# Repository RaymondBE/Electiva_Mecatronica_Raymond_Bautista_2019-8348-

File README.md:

# Electiva_Mecatronica_Raymond_Bautista_2019-8348-
Repositorio correspondiente a la asignatura de Diseño Mecatrónico. Raymond Bautista Espinosa (2019-8348).

Saludos:
Este repositorio contiene mis entregas realizadas en la asignatura de Diseño Mecatrónico. Período: 2022-C2, Universidad: ITLA.

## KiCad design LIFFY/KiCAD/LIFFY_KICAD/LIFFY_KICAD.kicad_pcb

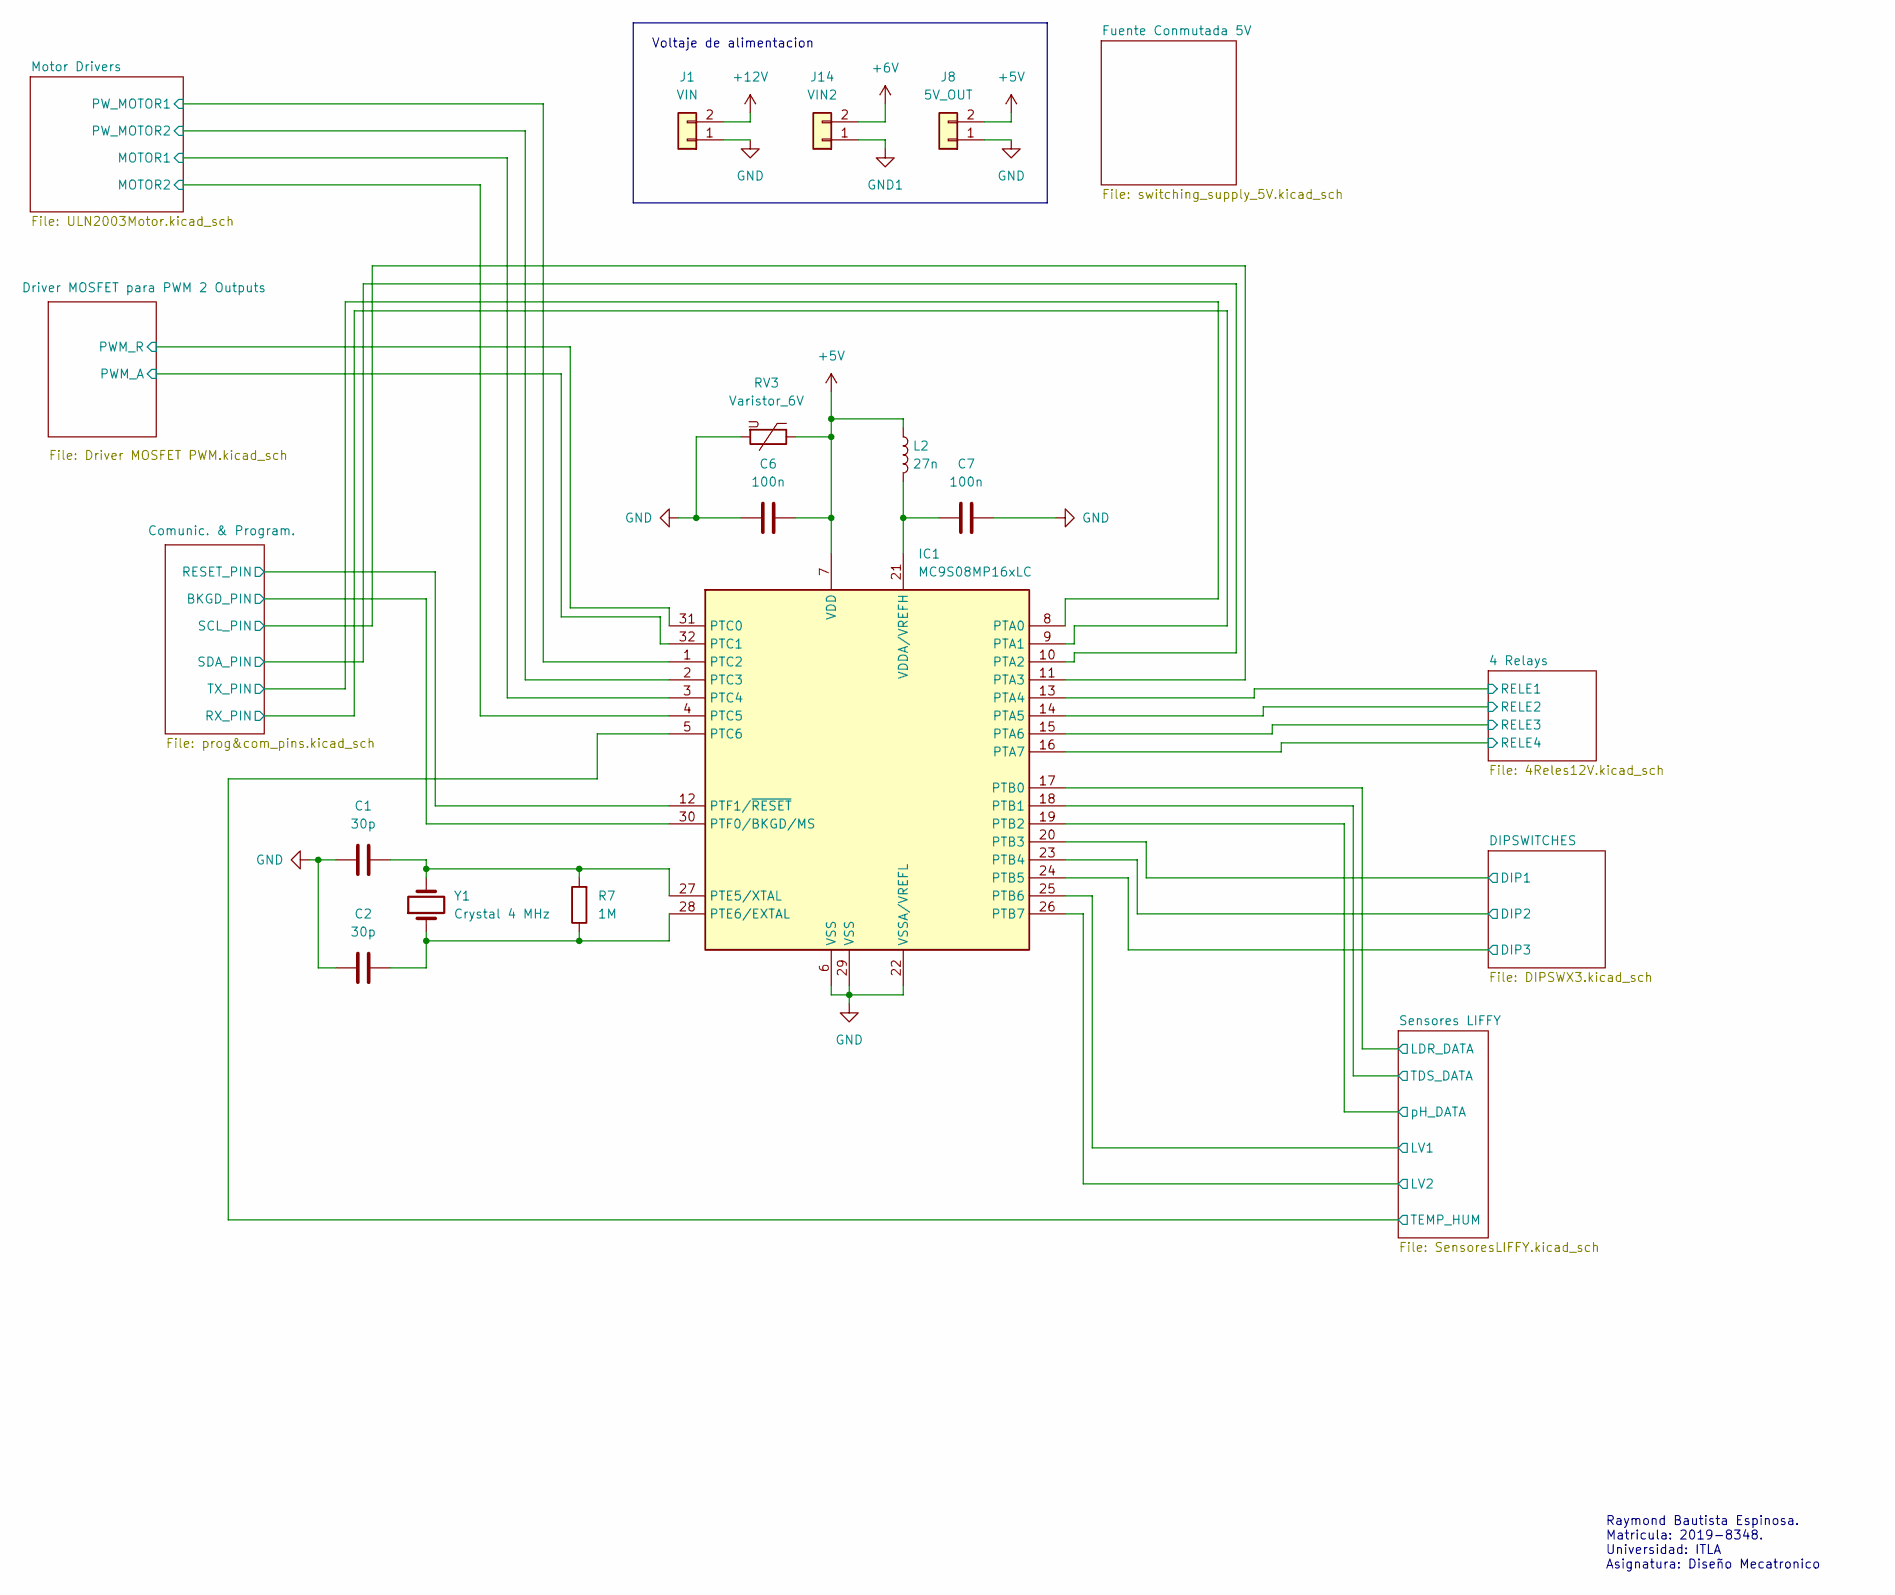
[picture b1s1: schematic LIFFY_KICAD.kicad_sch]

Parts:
C1, C2: 30p; C_0201_0603Metric
C6, C7: 100n; C_0201_0603Metric
IC1: MC9S08MP16xLC; LQFP-32_7x7mm_P0.8mm
J1: VIN; TerminalBlock_bornier-2_P5.08mm
J8: 5V_OUT; TerminalBlock_bornier-2_P5.08mm
J14: VIN2; TerminalBlock_bornier-2_P5.08mm
L2: 27n; L_0805_2012Metric
R7: 1M; R_0201_0603Metric
RV3: Varistor_6V; C_0805_2012Metric
Y1: Crystal 4 MHz; Crystal_HC49-4H_Vertical

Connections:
+5V: C6.2, IC1.7 (VDD), J8.2, L2.1, RV3.1; also elsewhere on the board
+6V: J14.2; also elsewhere on the board
+12V: J1.2; also elsewhere on the board
/4 Relays/RELE1: IC1.13 (PTA4); also elsewhere on the board
/4 Relays/RELE2: IC1.14 (PTA5); also elsewhere on the board
/4 Relays/RELE3: IC1.15 (PTA6); also elsewhere on the board
/4 Relays/RELE4: IC1.16 (PTA7); also elsewhere on the board
/Comunic. & Program./BKGD_PIN: IC1.30 (PTF0/BKGD/MS); also elsewhere on the board
/Comunic. & Program./RESET_PIN: IC1.12 (PTF1/~RESET); also elsewhere on the board
/Comunic. & Program./RX_PIN: IC1.9 (PTA1); also elsewhere on the board
/Comunic. & Program./SCL_PIN: IC1.11 (PTA3); also elsewhere on the board
/Comunic. & Program./SDA_PIN: IC1.10 (PTA2); also elsewhere on the board
/Comunic. & Program./TX_PIN: IC1.8 (PTA0); also elsewhere on the board
/DIPSWITCHES/DIP1: IC1.20 (PTB3); also elsewhere on the board
/DIPSWITCHES/DIP2: IC1.23 (PTB4); also elsewhere on the board
/DIPSWITCHES/DIP3: IC1.24 (PTB5); also elsewhere on the board
/Driver MOSFET para PWM 2 Outputs/PWM_A: IC1.32 (PTC1); also elsewhere on the board
/Driver MOSFET para PWM 2 Outputs/PWM_R: IC1.31 (PTC0); also elsewhere on the board
/Motor Drivers/MOTOR1: IC1.3 (PTC4); also elsewhere on the board
/Motor Drivers/MOTOR2: IC1.4 (PTC5); also elsewhere on the board
/Motor Drivers/PW_MOTOR1: IC1.1 (PTC2); also elsewhere on the board
/Motor Drivers/PW_MOTOR2: IC1.2 (PTC3); also elsewhere on the board
/Sensores LIFFY/LDR_DATA: IC1.17 (PTB0); also elsewhere on the board
/Sensores LIFFY/LV1: IC1.25 (PTB6); also elsewhere on the board
/Sensores LIFFY/LV2: IC1.26 (PTB7); also elsewhere on the board
/Sensores LIFFY/TDS_DATA: IC1.18 (PTB1); also elsewhere on the board
/Sensores LIFFY/TEMP_HUM: IC1.5 (PTC6); also elsewhere on the board
/Sensores LIFFY/pH_DATA: IC1.19 (PTB2); also elsewhere on the board
GND: C1.1, C2.1, C6.1, C7.1, IC1.6 (VSS), IC1.22 (VSSA/VREFL), IC1.29 (VSS), J1.1, J8.1, RV3.2; also elsewhere on the board
GND1: J14.1; also elsewhere on the board
unnamed: C1.2, IC1.27 (PTE5/XTAL), R7.2, Y1.2
unnamed: C2.2, IC1.28 (PTE6/EXTAL), R7.1, Y1.1
unnamed: C7.2, IC1.21 (VDDA/VREFH), L2.2

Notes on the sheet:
Raymond Bautista Espinosa. Matricula: 2019-8348. Universidad: ITLA Asignatura: Diseño Mecatronico
Voltaje de alimentacion

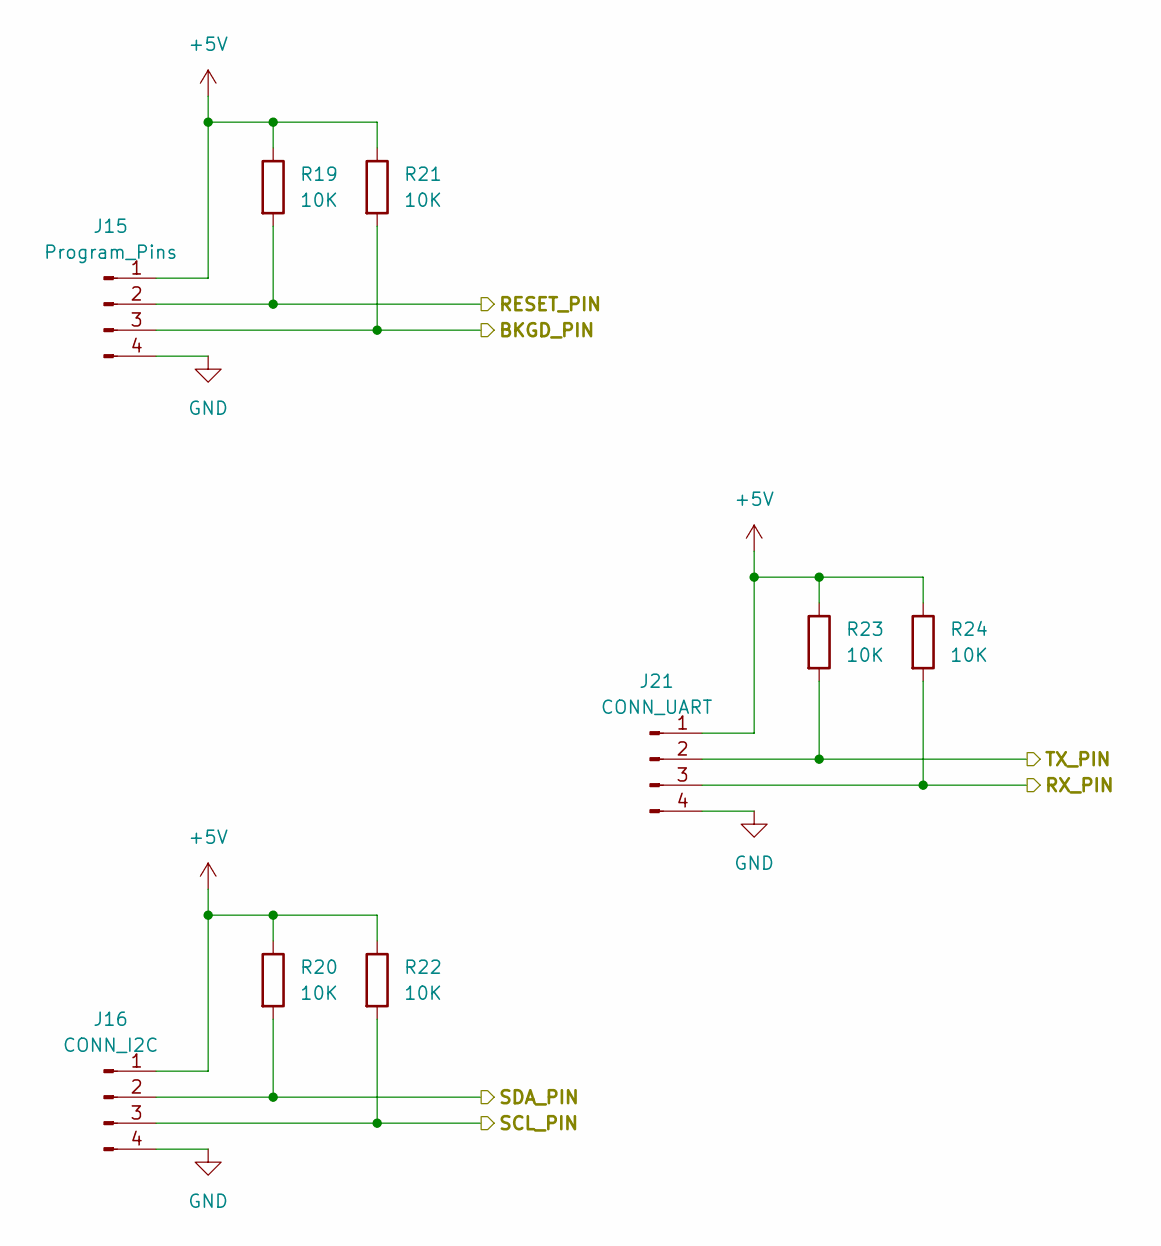
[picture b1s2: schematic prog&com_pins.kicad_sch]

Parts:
J15: Program_Pins; PinHeader_1x04_P2.54mm_Vertical
J16: CONN_I2C; PinHeader_1x04_P2.54mm_Vertical
J21: CONN_UART; PinHeader_1x04_P2.54mm_Vertical
R19, R20, R21, R22, R23, R24: 10K; R_0201_0603Metric

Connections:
+5V: J15.1, J16.1, J21.1, R19.1, R20.1, R21.1, R22.1, R23.1, R24.1; also elsewhere on the board
/Comunic. & Program./BKGD_PIN: J15.3, R21.2; also elsewhere on the board
/Comunic. & Program./RESET_PIN: J15.2, R19.2; also elsewhere on the board
/Comunic. & Program./RX_PIN: J21.3, R24.2; also elsewhere on the board
/Comunic. & Program./SCL_PIN: J16.3, R22.2; also elsewhere on the board
/Comunic. & Program./SDA_PIN: J16.2, R20.2; also elsewhere on the board
/Comunic. & Program./TX_PIN: J21.2, R23.2; also elsewhere on the board
GND: J15.4, J16.4, J21.4; also elsewhere on the board

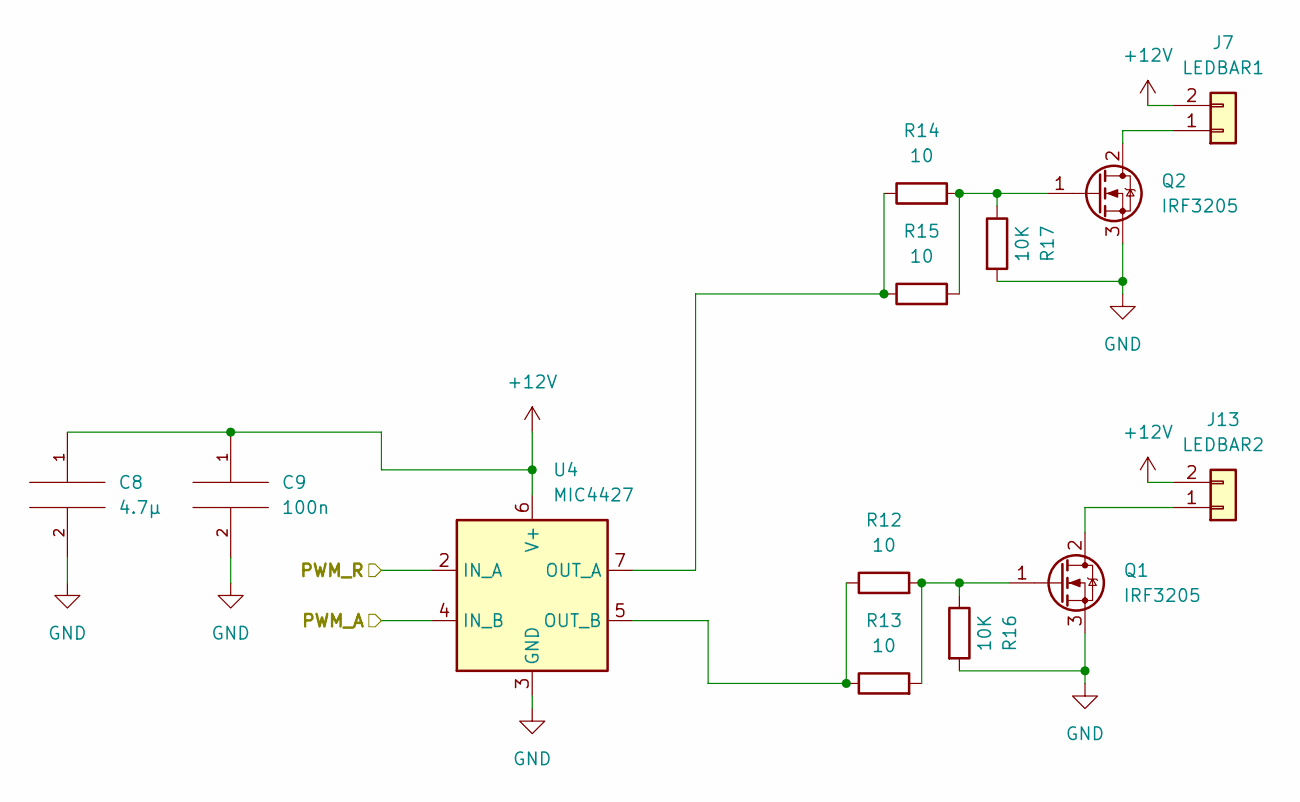
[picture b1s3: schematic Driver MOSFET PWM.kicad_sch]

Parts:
C8: 4.7µ; C_0805_2012Metric
C9: 100n; C_0201_0603Metric
J7: LEDBAR1; TerminalBlock_bornier-2_P5.08mm
J13: LEDBAR2; TerminalBlock_bornier-2_P5.08mm
Q1, Q2: IRF3205; TO-220-3_Vertical
R12, R13, R14, R15: 10; R_0201_0603Metric
R16, R17: 10K; R_0201_0603Metric
U4: MIC4427; SOIC-8_3.9x4.9mm_P1.27mm

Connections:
+12V: C8.1, C9.1, J7.2, J13.2, U4.6 (V+); also elsewhere on the board
/Driver MOSFET para PWM 2 Outputs/PWM_A: U4.4 (IN_B); also elsewhere on the board
/Driver MOSFET para PWM 2 Outputs/PWM_R: U4.2 (IN_A); also elsewhere on the board
GND: C8.2, C9.2, Q1.3 (S), Q2.3 (S), R16.2, R17.2, U4.3 (GND); also elsewhere on the board
unnamed: J7.1, Q2.2 (D)
unnamed: J13.1, Q1.2 (D)
unnamed: Q1.1 (G), R12.2, R13.2, R16.1
unnamed: Q2.1 (G), R14.2, R15.2, R17.1
unnamed: R12.1, R13.1, U4.5 (OUT_B)
unnamed: R14.1, R15.1, U4.7 (OUT_A)

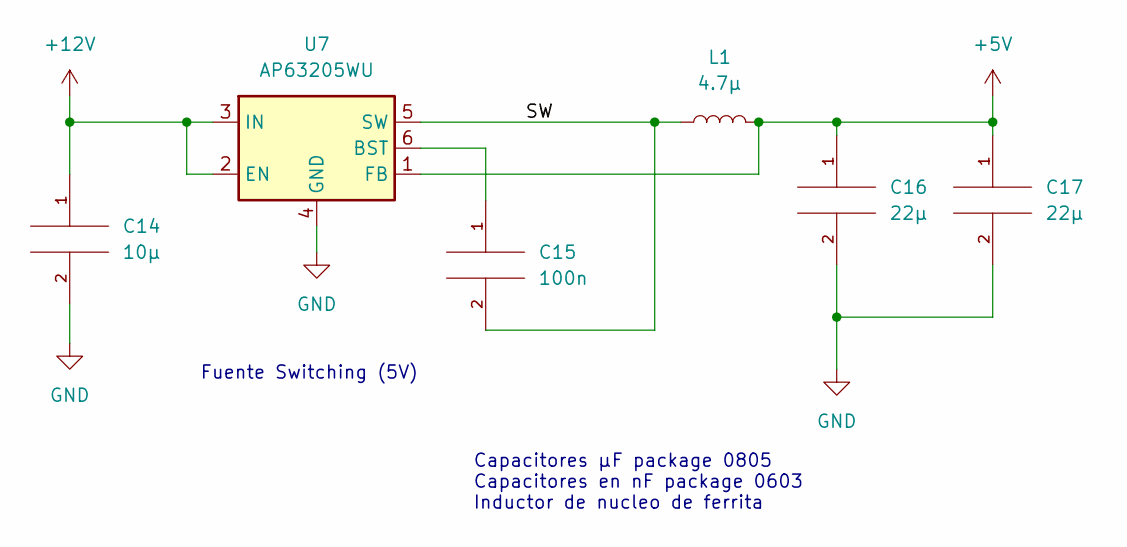
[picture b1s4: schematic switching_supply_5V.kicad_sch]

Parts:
C14: 10µ; C_0805_2012Metric
C15: 100n; C_0201_0603Metric
C16, C17: 22µ; C_0805_2012Metric
L1: 4.7µ; L_Bourns_SRN6045TA
U7: AP63205WU; TSOT-23-6

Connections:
+5V: C16.1, C17.1, L1.2, U7.1 (FB); also elsewhere on the board
+12V: C14.1, U7.2 (EN), U7.3 (IN); also elsewhere on the board
/Fuente Conmutada 5V/SW: C15.2, L1.1, U7.5 (SW)
GND: C14.2, C16.2, C17.2, U7.4 (GND); also elsewhere on the board
unnamed: C15.1, U7.6 (BST)

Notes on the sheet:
Fuente Switching (5V)
Capacitores µF package 0805 Capacitores en nF package 0603 Inductor de nucleo de ferrita

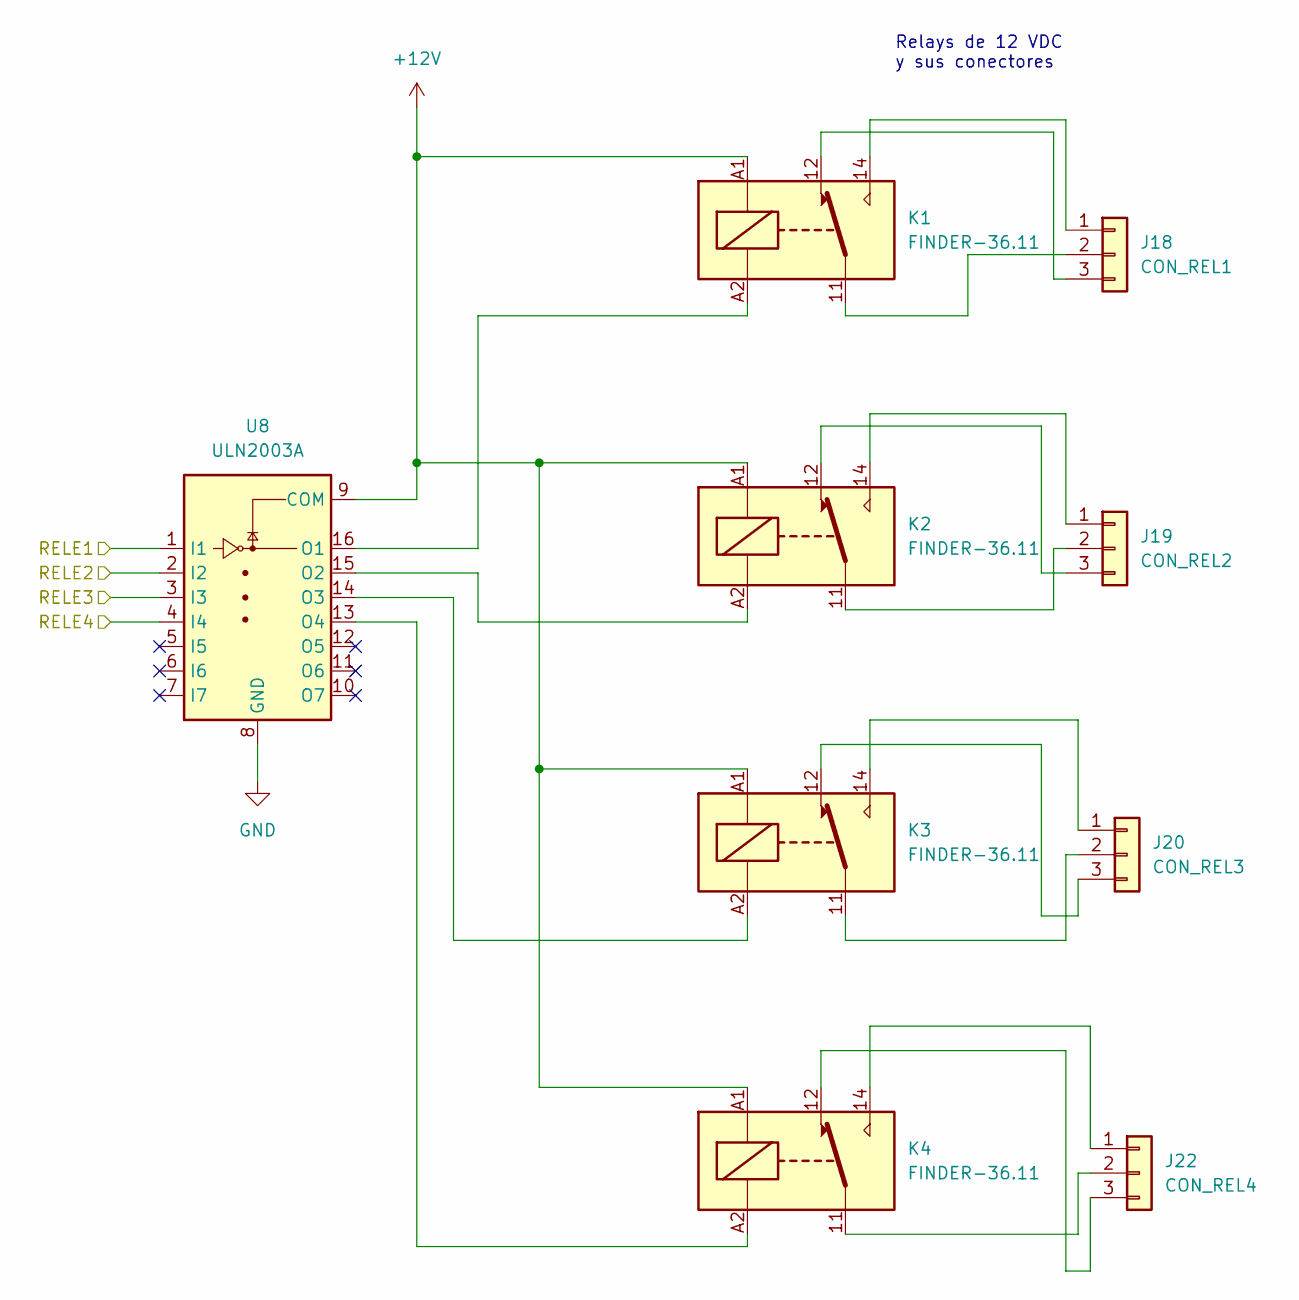
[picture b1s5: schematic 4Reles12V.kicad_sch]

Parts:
J18: CON_REL1; TerminalBlock_bornier-3_P5.08mm
J19: CON_REL2; TerminalBlock_bornier-3_P5.08mm
J20: CON_REL3; TerminalBlock_bornier-3_P5.08mm
J22: CON_REL4; TerminalBlock_bornier-3_P5.08mm
K1, K2, K3, K4: FINDER-36.11; Relay_SPDT_Finder_36.11
U8: ULN2003A; SOIC-16_3.9x9.9mm_P1.27mm

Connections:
+12V: K1.A1, K2.A1, K3.A1, K4.A1, U8.9 (COM); also elsewhere on the board
/4 Relays/RELE1: U8.1 (I1); also elsewhere on the board
/4 Relays/RELE2: U8.2 (I2); also elsewhere on the board
/4 Relays/RELE3: U8.3 (I3); also elsewhere on the board
/4 Relays/RELE4: U8.4 (I4); also elsewhere on the board
GND: U8.8 (GND); also elsewhere on the board
unnamed: J18.1, K1.14
unnamed: J18.2, K1.11
unnamed: J18.3, K1.12
unnamed: J19.1, K2.14
unnamed: J19.2, K2.11
unnamed: J19.3, K2.12
unnamed: J20.1, K3.14
unnamed: J20.2, K3.11
unnamed: J20.3, K3.12
unnamed: J22.1, K4.14
unnamed: J22.2, K4.11
unnamed: J22.3, K4.12
unnamed: K1.A2, U8.16 (O1)
unnamed: K2.A2, U8.15 (O2)
unnamed: K3.A2, U8.14 (O3)
unnamed: K4.A2, U8.13 (O4)

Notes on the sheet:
Relays de 12 VDC y sus conectores

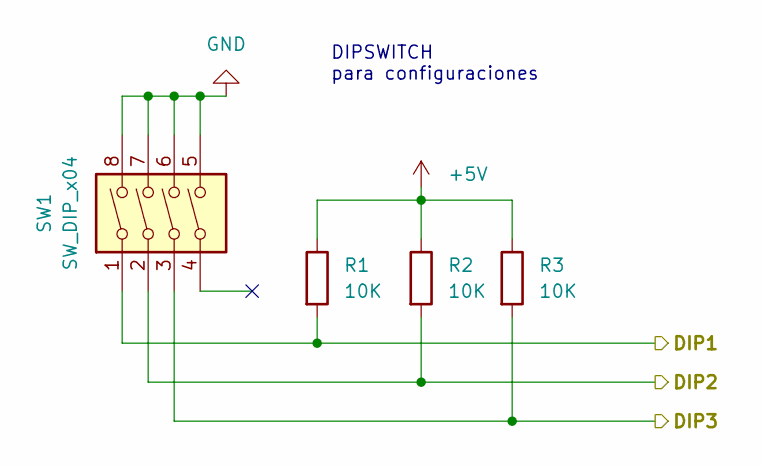
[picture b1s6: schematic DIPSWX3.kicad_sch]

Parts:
R1, R2, R3: 10K; R_0201_0603Metric
SW1: SW_DIP_x04; SW_DIP_SPSTx04_Slide_9.78x12.34mm_W8.61mm_P2.54mm

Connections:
+5V: R1.1, R2.1, R3.1; also elsewhere on the board
/DIPSWITCHES/DIP1: R1.2, SW1.1; also elsewhere on the board
/DIPSWITCHES/DIP2: R2.2, SW1.2; also elsewhere on the board
/DIPSWITCHES/DIP3: R3.2, SW1.3; also elsewhere on the board
GND: SW1.5, SW1.6, SW1.7, SW1.8; also elsewhere on the board

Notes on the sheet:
DIPSWITCH para configuraciones

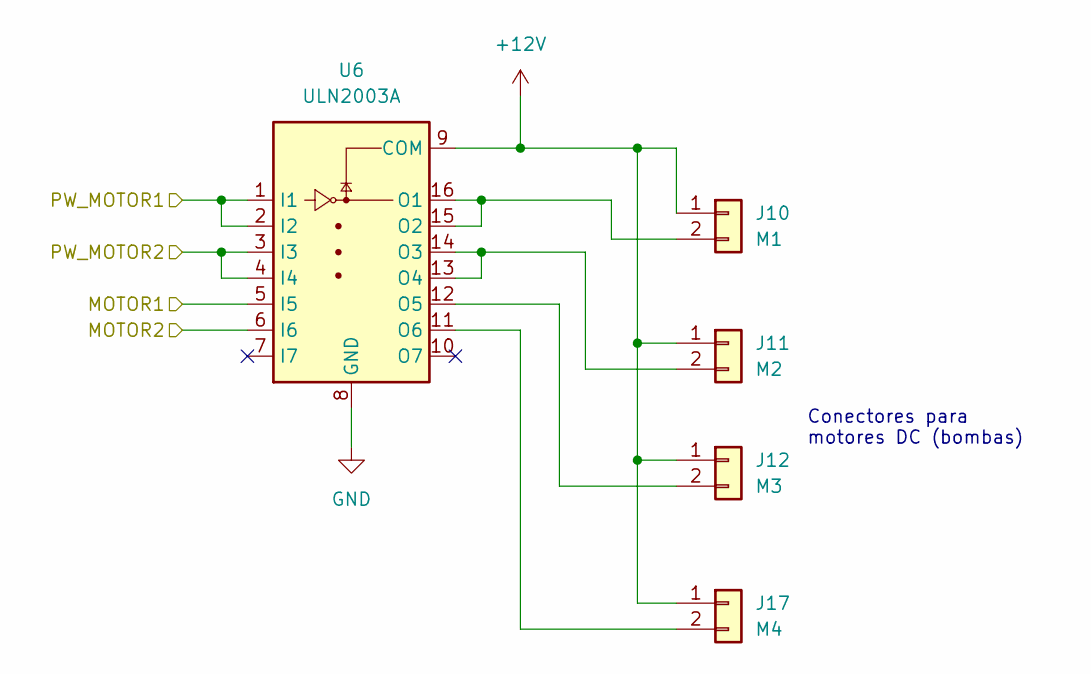
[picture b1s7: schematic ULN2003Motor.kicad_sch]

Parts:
J10: M1; TerminalBlock_bornier-2_P5.08mm
J11: M2; TerminalBlock_bornier-2_P5.08mm
J12: M3; TerminalBlock_bornier-2_P5.08mm
J17: M4; TerminalBlock_bornier-2_P5.08mm
U6: ULN2003A; SOIC-16_3.9x9.9mm_P1.27mm

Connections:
+12V: J10.1, J11.1, J12.1, J17.1, U6.9 (COM); also elsewhere on the board
/Motor Drivers/MOTOR1: U6.5 (I5); also elsewhere on the board
/Motor Drivers/MOTOR2: U6.6 (I6); also elsewhere on the board
/Motor Drivers/PW_MOTOR1: U6.1 (I1), U6.2 (I2); also elsewhere on the board
/Motor Drivers/PW_MOTOR2: U6.3 (I3), U6.4 (I4); also elsewhere on the board
GND: U6.8 (GND); also elsewhere on the board
unnamed: J10.2, U6.15 (O2), U6.16 (O1)
unnamed: J11.2, U6.13 (O4), U6.14 (O3)
unnamed: J12.2, U6.12 (O5)
unnamed: J17.2, U6.11 (O6)

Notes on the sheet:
Conectores para motores DC (bombas)

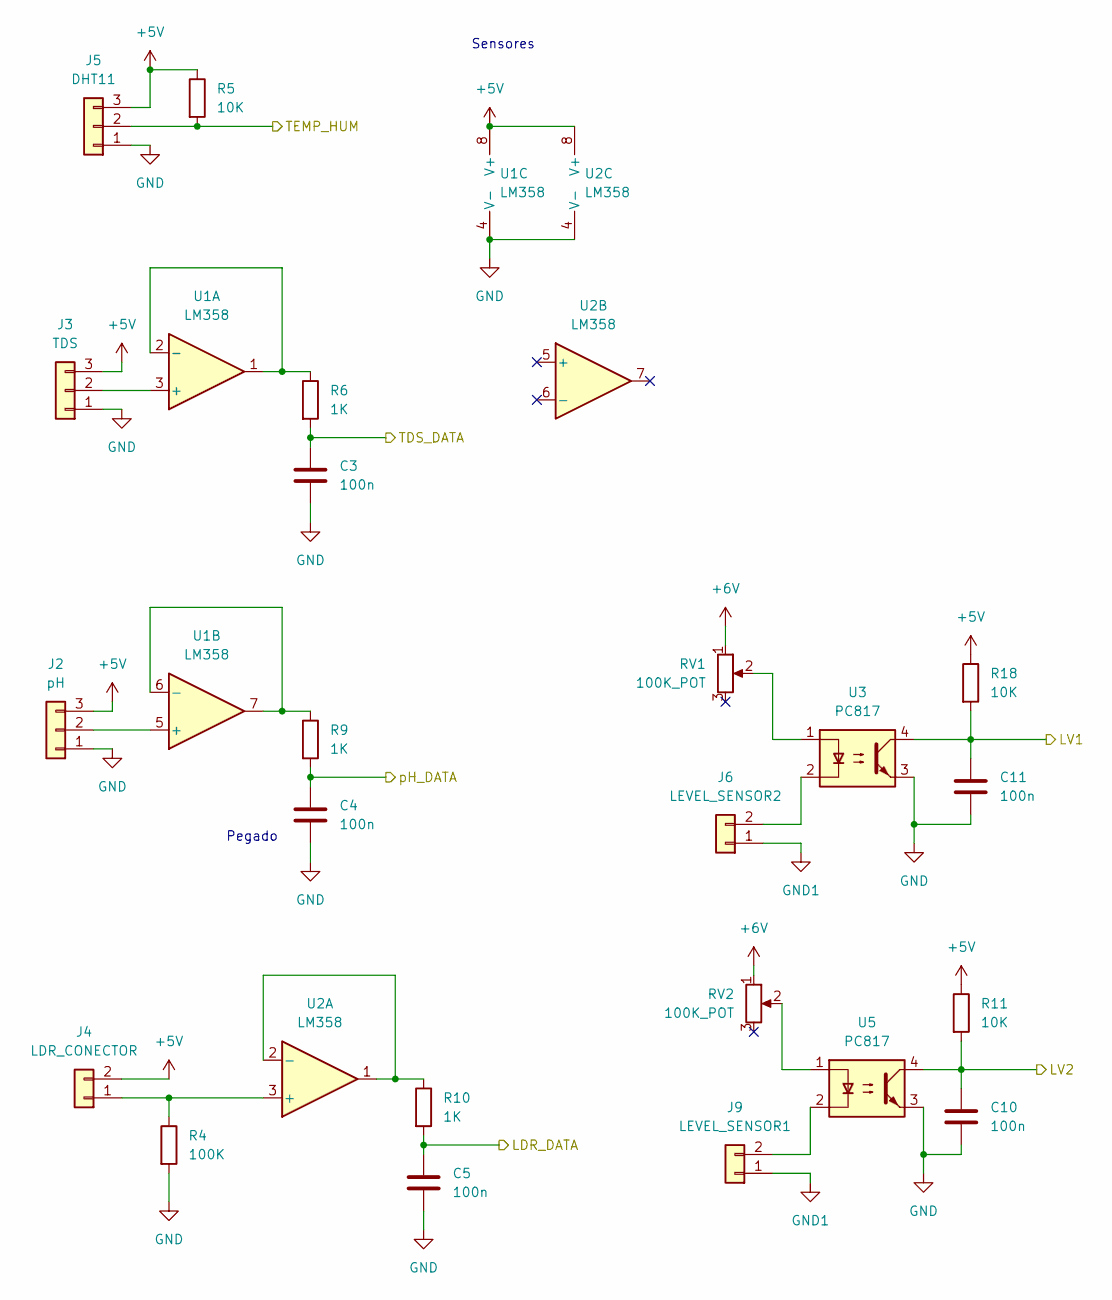
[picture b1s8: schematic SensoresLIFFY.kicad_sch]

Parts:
C3, C4, C5, C10, C11: 100n; C_0201_0603Metric
J2: pH; TerminalBlock_bornier-3_P5.08mm
J3: TDS; TerminalBlock_bornier-3_P5.08mm
J4: LDR_CONECTOR; TerminalBlock_bornier-2_P5.08mm
J5: DHT11; TerminalBlock_bornier-3_P5.08mm
J6: LEVEL_SENSOR2; TerminalBlock_bornier-2_P5.08mm
J9: LEVEL_SENSOR1; TerminalBlock_bornier-2_P5.08mm
R4: 100K; R_0201_0603Metric
R5, R11, R18: 10K; R_0201_0603Metric
R6, R9, R10: 1K; R_0201_0603Metric
RV1, RV2: 100K_POT; Potentiometer_Bourns_3296Y_Vertical
U1, U2: LM358; SOIC-8_3.9x4.9mm_P1.27mm
U3, U5: PC817; SMDIP-4_W7.62mm

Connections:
+5V: J2.3, J3.3, J4.2, J5.3, R5.1, R11.1, R18.1, U1.8 (V+), U2.8 (V+); also elsewhere on the board
+6V: RV1.1, RV2.1; also elsewhere on the board
/Sensores LIFFY/LDR_DATA: C5.1, R10.2; also elsewhere on the board
/Sensores LIFFY/LV1: C11.1, R18.2, U3.4; also elsewhere on the board
/Sensores LIFFY/LV2: C10.1, R11.2, U5.4; also elsewhere on the board
/Sensores LIFFY/TDS_DATA: C3.1, R6.2; also elsewhere on the board
/Sensores LIFFY/TEMP_HUM: J5.2, R5.2; also elsewhere on the board
/Sensores LIFFY/pH_DATA: C4.1, R9.2; also elsewhere on the board
GND: C3.2, C4.2, C5.2, C10.2, C11.2, J2.1, J3.1, J5.1, R4.2, U1.4 (V-), U2.4 (V-), U3.3, U5.3; also elsewhere on the board
GND1: J6.1, J9.1; also elsewhere on the board
unnamed: J2.2, U1.5 (+)
unnamed: J3.2, U1.3 (+)
unnamed: J4.1, R4.1, U2.3 (+)
unnamed: J6.2, U3.2
unnamed: J9.2, U5.2
unnamed: R6.1, U1.1, U1.2 (-)
unnamed: R9.1, U1.6 (-), U1.7
unnamed: R10.1, U2.1, U2.2 (-)
unnamed: RV1.2, U3.1
unnamed: RV2.2, U5.1

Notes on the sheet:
Sensores
Pegado

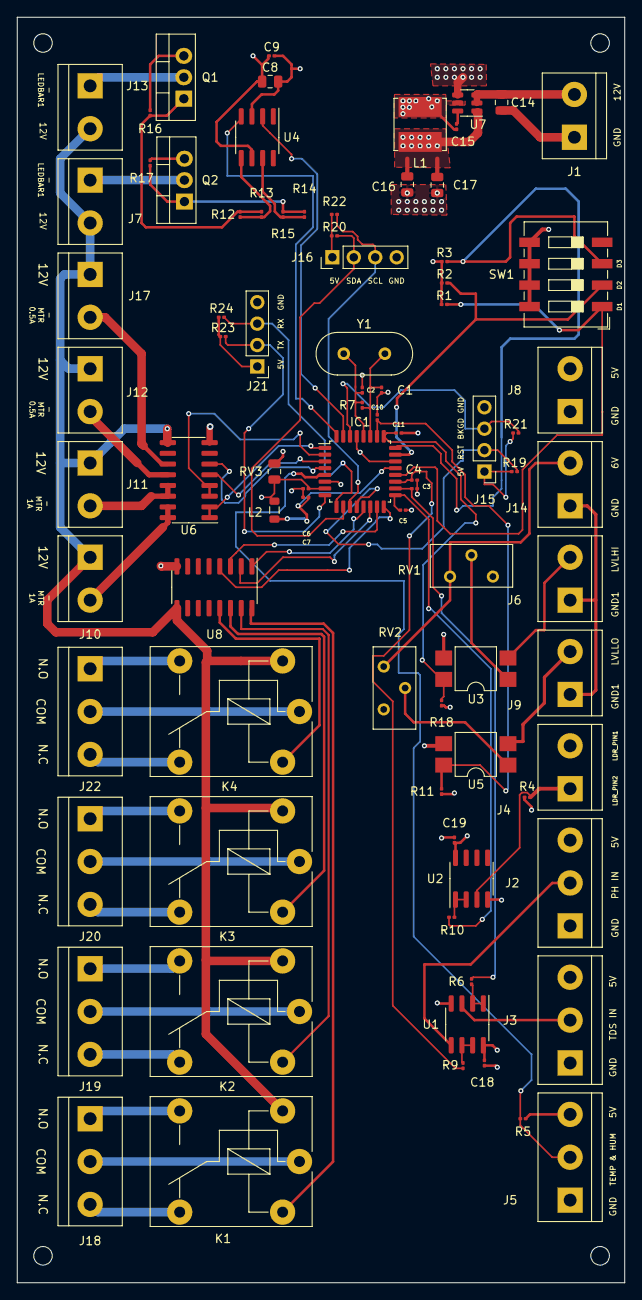
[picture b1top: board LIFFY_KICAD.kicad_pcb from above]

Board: 4 copper layers, 72.0 x 150.0 mm, 88 parts (0 on the bottom side), 71 nets.

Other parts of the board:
C18, C19: 100n; C_0201_0603Metric
HOLE1, HOLE2, HOLE3, HOLE4: MountingHole_2.2mm_M2

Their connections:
+5V: C18.1, C19.1; also elsewhere on the board
GND: C18.2, C19.2; also elsewhere on the board

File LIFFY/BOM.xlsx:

|  | Part Number | References | Value | Footprint | Quantity
 |  | 1 | C3, C4, C5, C6, C7, C9, C10, C11, C15, C18, C19 | 100n | C_0201_0603Metric | 11
 |  | 2 | C1, C2 | 30p | C_0201_0603Metric | 2
 |  | 3 | C16, C17 | 22µ | C_0805_2012Metric | 2
 |  | 4 | C8 | 4.7µ | C_0805_2012Metric | 1
 |  | 5 | C14 | 10µ | C_0805_2012Metric | 1
 |  | 6 | R1, R2, R3, R5, R8, R11, R16, R17, R18, R19, R20, R21, R22, R23, R24 | 10K | R_0201_0603Metric | 15
 |  | 7 | R12, R13, R14, R15 | 10 | R_0201_0603Metric | 4
 |  | 8 | R6, R9, R10 | 1K | R_0201_0603Metric | 3
 |  | 9 | R4 | 100K | R_0201_0603Metric | 1
 |  | 10 | R7 | 1M | R_0201_0603Metric | 1
 |  | 11 | L1 | 4.7µ | L_Bourns_SRN6045TA | 1
 |  | 12 | L2 | 27n | L_0805_2012Metric | 1
 |  | 13 | U1, U2 | LM358 | SOIC-8_3.9x4.9mm_P1.27mm | 2
 |  | 14 | U3, U5 | PC817 | SMDIP-4_W7.62mm | 2
 |  | 15 | U6, U8 | ULN2003A | SOIC-16_3.9x9.9mm_P1.27mm | 2
 |  | 16 | U4 | MIC4427 | SOIC-8_3.9x4.9mm_P1.27mm | 1
 |  | 17 | U7 | AP63205WU | TSOT-23-6 | 1
 |  | 18 | Y1 | Crystal 4 MHz | Crystal_HC49-4H_Vertical | 1
 |  | 19 | SW1 | SW_DIP_x04 | SW_DIP_SPSTx04_Slide_9.78x12.34mm_W8.61mm_P2.54mm | 1
 |  | 20 | K1, K2, K3, K4 | FINDER-36.11 | Relay_SPDT_Finder_36.11 | 4
 |  | 21 | Q1, Q2 | IRF3205 | TO-220-3_Vertical | 2
 |  | 22 | RV1, RV2 | 100K_POT | Potentiometer_Bourns_3296Y_Vertical | 2
 |  | 23 | IC1 | MC9S08MP16xLC | LQFP-32_7x7mm_P0.8mm | 1
 |  | 24 | RV3 | Varistor_6V | C_0805_2012Metric | 1
 |  | 25 | J1 | VIN | TerminalBlock_bornier-2_P5.08mm | 1
 |  | 26 | J2 | pH | TerminalBlock_bornier-3_P5.08mm | 1
 |  | 27 | J3 | TDS | TerminalBlock_bornier-3_P5.08mm | 1
 |  | 28 | J4 | LDR_CONECTOR | TerminalBlock_bornier-2_P5.08mm | 1
 |  | 29 | J5 | DHT11 | TerminalBlock_bornier-3_P5.08mm | 1
 |  | 30 | J6 | LEVEL_SENSOR2 | TerminalBlock_bornier-2_P5.08mm | 1
 |  | 31 | J7 | LEDBAR1 | TerminalBlock_bornier-2_P5.08mm | 1
 |  | 32 | J8 | 5V_OUT | TerminalBlock_bornier-2_P5.08mm | 1
 |  | 33 | J9 | LEVEL_SENSOR1 | TerminalBlock_bornier-2_P5.08mm | 1
 |  | 34 | J10 | M1 | TerminalBlock_bornier-2_P5.08mm | 1
 |  | 35 | J11 | M2 | TerminalBlock_bornier-2_P5.08mm | 1
 |  | 36 | J12 | M3 | TerminalBlock_bornier-2_P5.08mm | 1
 |  | 37 | J13 | LEDBAR2 | TerminalBlock_bornier-2_P5.08mm | 1
 |  | 38 | J14 | VIN2 | TerminalBlock_bornier-2_P5.08mm | 1
 |  | 39 | J15 | Program_Pins | PinHeader_1x04_P2.54mm_Vertical | 1
 |  | 40 | J16 | CONN_I2C | PinHeader_1x04_P2.54mm_Vertical | 1
 |  | 41 | J17 | M4 | TerminalBlock_bornier-2_P5.08mm | 1
 |  | 42 | J18 | CON_REL1 | TerminalBlock_bornier-3_P5.08mm | 1
 |  | 43 | J19 | CON_REL2 | TerminalBlock_bornier-3_P5.08mm | 1
 |  | 44 | J20 | CON_REL3 | TerminalBlock_bornier-3_P5.08mm | 1
 |  | 45 | J21 | CONN_UART | PinHeader_1x04_P2.54mm_Vertical | 1
 |  | 46 | J22 | CON_REL4 | TerminalBlock_bornier-3_P5.08mm | 1

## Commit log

2022-06-09 Version 1 de la plantilla de requisitos.
2022-06-09 Logo de MI Controller Solutions
2022-06-09 Elimine el logo
2022-06-09 Logo anexado a carpeta
2022-06-09 Logo removido 2
2022-06-10 V2_Nuevo Logo Agregado
2022-06-10 logo v2
2022-06-10 Notas de Investigación V1
2022-06-17 V2 13 Investigaciones
2022-07-01 V3 Investigaciones
2022-07-08 V1 LIFFY Files
2022-07-15 V2 PCB ADDED
2022-07-15 V4 Investigaciones
2022-07-22 V3 Fixed
2022-07-22 V4.5 Fixed
2022-07-22 V5 Aprobado
2022-07-22 V6 Notas de silkscreen añadidas
2022-07-22 V7 Archivos Gerber añadidos
2022-07-25 V7.5 Gerber Added
